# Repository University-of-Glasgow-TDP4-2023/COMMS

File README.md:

# TDP4 Comms team

## Display
To use any display code you must download the modified constructor and place it in the u8g2 library. This is `Documents/Arduino/libraries/u8g2/src/clib` if you're using the Arduino IDE. The following lines must also be included in any code to run properly. The constructor just after inclusion of any libraries `U8G2_ST7586S_YMC240160_F_6800 u8g2(U8G2_R0, 0, 1, 2, 3, 4, 5, 6, 7, 8, 9, 10, 11);` and `u8g2.setContrast(65);` in setup just after `u8g2.begin();`.

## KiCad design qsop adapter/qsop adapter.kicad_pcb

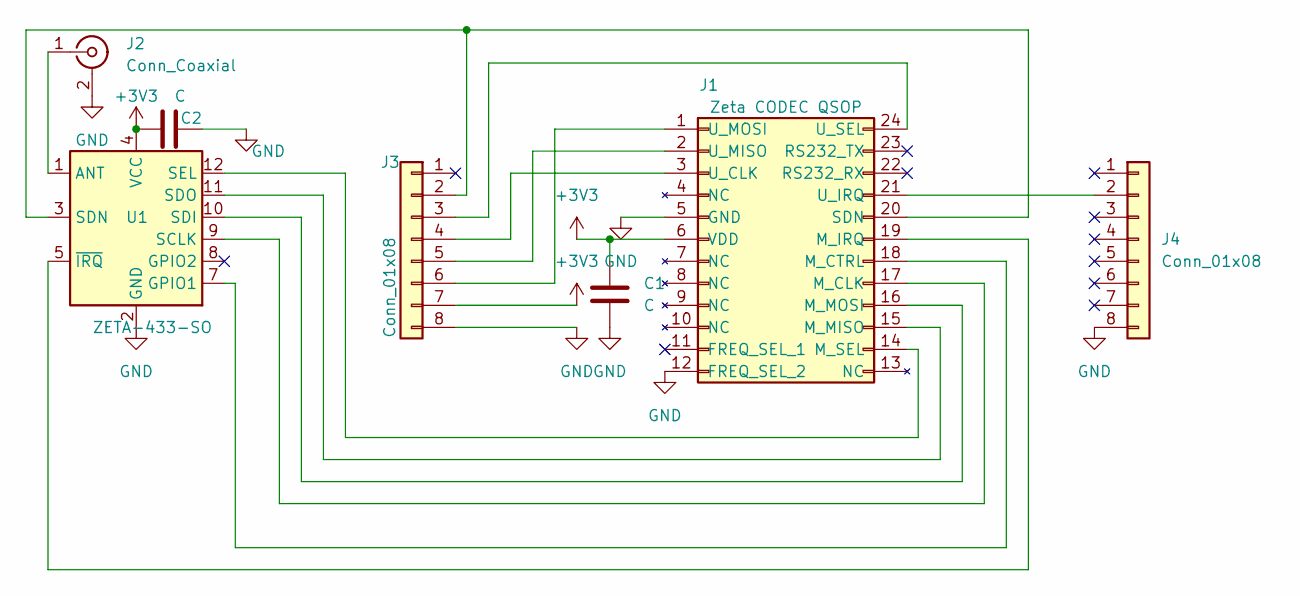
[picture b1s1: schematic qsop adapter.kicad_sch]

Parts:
C1, C2: C; C_0805_2012Metric_Pad1.18x1.45mm_HandSolder
J1: Zeta CODEC QSOP; QSOP-24_3.9x8.7mm_P0.635mm
J2: Conn_Coaxial; U.FL_Hirose_U.FL-R-SMT-1_Vertical
J3, J4: Conn_01x08; PinHeader_1x08_P2.54mm_Vertical
U1: ZETA-433-SO; ZETA-433-SO_SMD

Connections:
+3V3: C1.1, C2.1, J1.6 (VDD), J3.7, U1.4 (VCC)
GND: C1.2, C2.2, J1.5 (GND), J1.12 (FREQ_SEL_2), J2.2 (Ext), J3.8, J4.8, U1.2 (GND)
unnamed: J1.17 (M_CLK), U1.9 (SCLK)
unnamed: J1.18 (M_CTRL), U1.7 (GPIO1)
unnamed: J1.19 (M_IRQ), U1.5 (~IRQ)
unnamed: J1.15 (M_MISO), U1.11 (SDO)
unnamed: J1.16 (M_MOSI), U1.10 (SDI)
unnamed: J1.14 (M_SEL), U1.12 (SEL)
unnamed: J1.20 (SDN), J3.2, U1.3 (SDN)
unnamed: J1.3 (U_CLK), J3.4
unnamed: J1.21 (U_IRQ), J4.2
unnamed: J1.2 (U_MISO), J3.5
unnamed: J1.1 (U_MOSI), J3.6
unnamed: J1.24 (U_SEL), J3.3
unnamed: J2.1 (In), U1.1 (ANT)

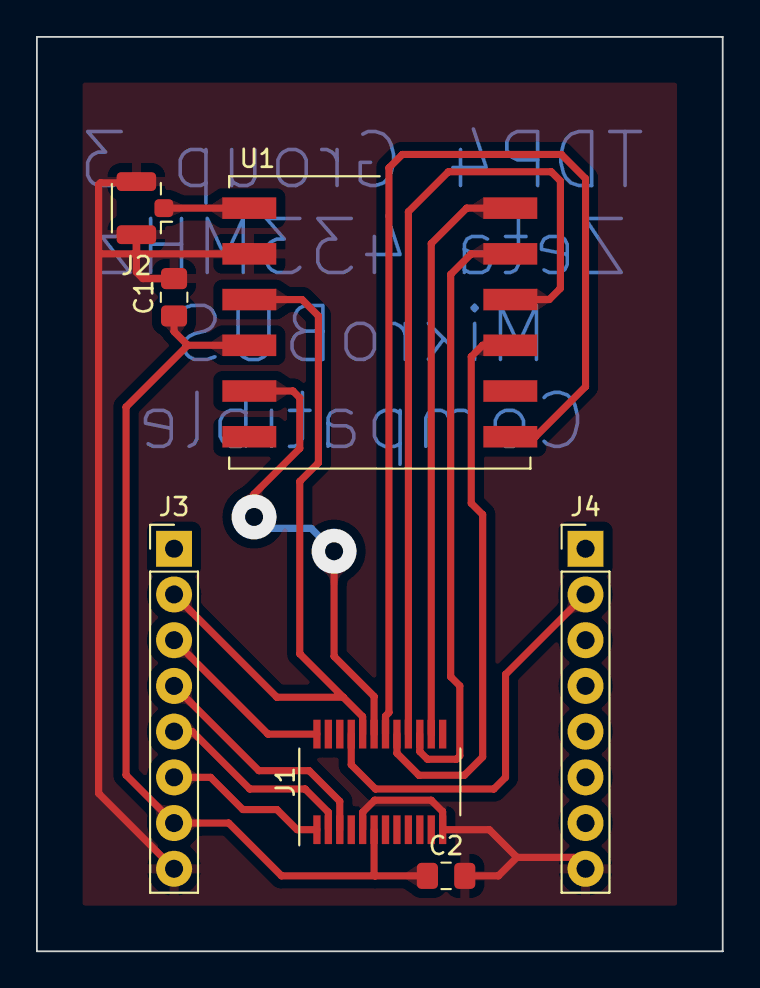
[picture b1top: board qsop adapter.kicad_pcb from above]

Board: 2 copper layers, 38.1 x 50.8 mm, 7 parts (0 on the bottom side), 15 nets.

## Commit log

2024-01-23 Added report
2024-01-23 Display test software
    outputs spi signal, not sure if compatible with display
2024-01-30 sample u8g2 display code added
2024-01-31 Modded constructor and graphics test
    add constructor to your u8g2 library and overwrite
2024-01-31 Test to check different orientations
2024-02-01 Basic display code initial commit
    Has the percentage line and a few bits of text
2024-02-02 Initial Schematic
    Includes display and a battery cell, no buttons yet. Needs cross-referenced with current breadboard.
2024-02-02 Added instructions for display and kicad
2024-02-06 Updated KiCad model
2024-02-06 Fixed entirely
    Both flipmodes work, default should be unflipped
2024-02-08 RF Initial Commit + Bidirectional Data Transfer
    Transfers "John" from one RF transceiver to the other upon a button press, then once sent the receiving Pico will turn its LED off
    LEDs on pin 15, button on pin 14
    As of now, LEDs currently do not work, RF untested due to lack of antennae
2024-02-13 Fixed LED
2024-02-13 USB output working and comparison fixed
2024-02-13 Updated GitIgnore
2024-02-13 Added commands to send (and turn on the LED)
2024-02-20 NRF Transmitting when 1 pressed, LED on
2024-02-20 Fixed gitignore
2024-02-20 updated ignored
2024-02-21 display prototype ish
2024-02-22 Adapter to convert Zeta+Codec to MikroBUS
2024-02-27 Alternative TX code stored for later use
2024-03-14 reactive!
2024-03-14 Added very cursed transceiver code
2024-03-20 added more reactivity
2024-03-21 pretty much everything
2024-04-17 Updated Pins
    Updated battery low indicator pin from 12 to 13 to function on motherboard
2024-04-17 Updated constructor for new pins
    Need to test that this still works
2024-04-17 Updated Pins
    Changed A0 pin (speed selector) from 15 to 26. Changed pins 9 and 10 to 9 and 2 as the constructor has now changed.
2024-05-02 send big number
2024-05-02 Execute Payload working
    TODO: Create payloads depending on inputs
2024-05-02 Execute and Create packets working for commands
    TODO: Add functionality for Data Transfer as well as commands
2024-05-02 4 bit data packet also transferred
2024-05-02 Fixed packet format
2024-05-09 merged code
2024-05-14 Display and Transceiver integrated with Motor
2024-05-15 Direction button added
2024-05-16 Stabilisation off and attempted display switch
2024-05-16 slight changes
2024-05-16 added error stuff
2024-05-18 refactoring
2024-05-19 FINAL ONE RAAAAH
